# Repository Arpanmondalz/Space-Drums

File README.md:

# Space Drums

Space Drums is an open source computer vision-based air drumming system. It utilizes a smartphone as a wireless camera to track hand positions via MediaPipe and ESP32-based drumsticks to trigger hits via UDP.

This project enables a virtual drum kit experience in mid-air with real-time audio feedback.

---

## Project Structure

The repository is organized into three primary components:

*   **linux-server/**: The optimized Python server for Linux systems. Recommended for lowest latency.
*   **windows-server/**: The standard Python server for Windows 10 and 11.
*   **firmware/**: C++ firmware for the ESP32-based drumsticks.

---

## Hardware Requirements

*   **Computer**: A laptop or desktop running Linux (Ubuntu/Mint) or Windows 10/11.
*   **Smartphone**: Any modern smartphone with a camera and web browser (used as the video source).
*   **Space Drum sticks**
*   **Network**: Both the computer and smartphone must be connected to the same WiFi network.

---

## Version Comparison

### Linux Version (Recommended)
Optimized for high performance. It utilizes direct kernel access for video (V4L2) and audio (ALSA), achieving sub-10ms audio response and superior frame rate stability. It supports high-priority process scheduling.

### Windows Version
Easier to set up using standard Windows drivers (DirectShow). While latency is slightly higher due to the Windows audio stack, it is fully functional for standard use.

---

## Installation and Setup

### 1. ESP32 Firmware
Flash the code located in the `firmware/` folder to your ESP32 boards.

1.  Open the project in the Arduino IDE or PlatformIO.
2.  Update the WiFi credentials (`SSID` and `PASSWORD`) in the source code.
3.  Flash one stick configured as **LEFT** and the other as **RIGHT** (refer to the definitions at the top of the firmware file).

### 2. Python Server Setup
Ensure Python 3.10 or newer is installed.

#### Linux Setup
Navigate to the `linux-server/` directory and run:
```bash
sudo apt-get install libgl1 libasound2-dev
python3 -m venv venv
source venv/bin/activate
pip install -r requirements.txt
```
*Note: Granting high-priority permissions to the Python executable is recommended for optimal performance.*

#### Windows Setup
Navigate to the `windows-server/` directory in PowerShell:
```powershell
python -m venv venv
.\venv\Scripts\Activate
pip install -r requirements.txt
```

### 3. Audio Files

All audio files can be downloaded from the sounds/ folder

---

## Running the System

1.  **Start the Server:**
    *   **Linux:** `venv/bin/python main.py`
    *   **Windows:** `python main.py`

2.  **Connect the Camera:**
    *   The terminal will display a local IP address (e.g., `http://192.168.1.15:5000`).
    *   Open this address in your smartphone's web browser.
    *   Select **Connect** and grant camera permissions.
    *   Position the phone camera to capture your movements.

3.  **Power on the Sticks:**
    *   Turn on the ESP32 drumsticks.
    *   Only the first time: You will need to connect to the "AirDrums-Stick" wifi network and add your wifi SSID and password for each stick
    *   They will automatically discover the server over UDP.
    *   A confirmation sound will play once both sticks are synchronized.

---

## Troubleshooting

*   **Firewall:** Ensure the computer allows incoming connections on **TCP port 5000** (Video) and **UDP port 5556** (Drum Hits).
*   **Audio Latency:**
    *   **Linux:** Ensure you are using the ALSA configuration provided in the code.
    *   **Windows:** If jitter occurs, set the Python process priority to "Realtime" in the Task Manager.

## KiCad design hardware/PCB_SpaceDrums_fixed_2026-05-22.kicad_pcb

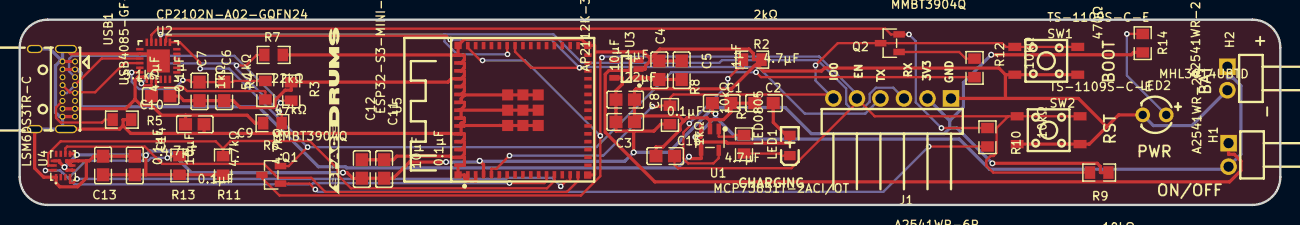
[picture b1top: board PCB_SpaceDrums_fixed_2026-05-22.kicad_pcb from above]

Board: 2 copper layers, 136.1 x 20.0 mm, 44 parts (0 on the bottom side), 28 nets.

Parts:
C1, C2, C7, C10: 4.7µF; C0805
C3: 22µF; C0805
C4, C12, C14: 10µF; C0805
C5, C8: 1µF; C0805
C6, C9, C11, C13, C15: 0.1µF; C0805
H1, H2: A2541WR-2P; HDR-TH_2P-P2.54-H-M-W10.0
J1: A2541WR-6P; HDR-TH_6P-P2.54-H-M-W10.3
LED1: LED0805; LED0805-RD
LED2: MHL3014UBTD; LED-TH_BD3.9-P2.54-RD
Q1, Q2: MMBT3904Q; SOT-23-3_L2.9-W1.3-P1.90-LS2.4-BR
R1, R4: 1kΩ; R0805
R2: 2kΩ; R0805
R3, R5: 5.1kΩ; R0805
R6: 22kΩ; R0805
R7: 47kΩ; R0805
R8, R9, R10, R12: 10kΩ; R0805
R11, R13: 4.7kΩ; R0805
R14: 470Ω; R0805
SW1, SW2: TS-1109S-C-E; SW-SMD_4P-L4.5-W4.5-P3.00-LS7.0
U1: MCP73831T-2ACI/OT; SOT-23-5_L3.0-W1.7-P0.95-LS2.8-BL
U2: CP2102N-A02-GQFN24; QFN-24_L4.0-W4.0-P0.50-TL-EP2.5
U3: AP2112K-3.3TRG1; SOT-25-5_L2.9-W1.6-P0.95-LS2.8-BL
U4: LSM6DS3TR-C; LGA-14_L3.0-W2.5-P0.50-TL
U5: ESP32-S3-MINI-1-N8; BULETM-SMD_ESP32-S3-MINI-1-N8
USB1: USB4085-GF-A; USC-C-SMD_USB4085-GF-A

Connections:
3V3: C3.1, C8.1, C11.2, C12.2, C13.2, C14.2, J1.2, R8.2, R9.1, R11.2, R13.2, R14.1, U3.5, U4.5, U4.8, U4.12, U5.3
BAT+: C1.2, H1.2, H2.1, U1.3
CP_8: R6.2, R7.2, U2.8
CP_RX: J1.4, U2.20, U5.39
CP_TX: J1.3, U2.21, U5.40
D+: U2.3, USB1.A6, USB1.B6
D-: U2.4, USB1.A7, USB1.B7
DTR: Q2.2, R10.1, U2.23
EN: C15.2, J1.5, Q1.3, R9.2, SW2.1, SW2.2, U5.45
GND: C1.1, C2.1, C3.2, C4.2, C5.1, C6.1, C7.1, C8.2, C9.1, C10.1, C11.1, C12.1, C13.1, C14.1, C15.1, H2.2, J1.1, LED2.1, R2.2, R3.2, R5.2, R7.1, SW1.3, SW1.4, SW2.3, SW2.4, U1.2, U2.2, U2.25, U3.2, U4.1, U4.6, U4.7, U5.1, U5.2, U5.46, U5.47, U5.48, U5.49, U5.50, U5.51, U5.52, U5.53, U5.54, U5.55, U5.56, U5.57, U5.58, U5.59, U5.60, U5.GND, USB1.A1, USB1.A12, USB1.B1, USB1.B12, USB1.S1
INT1: U4.4, U5.14
INT2: U4.9, U5.15
IO0: J1.6, Q2.3, R8.1, SW1.1, SW1.2, U5.4
LED2_2: LED2.2, R14.2
Q1_1: Q1.1, R10.2
Q2_1: Q2.1, R12.1
R1_1: LED1.1, R1.1
RTS: Q1.2, R12.2, U2.19
SCL: R11.1, U4.13, U5.12
SDA: R13.1, U4.14, U5.11
U1_1: R1.2, U1.1
U1_5: R2.1, U1.5
U2_5: C6.2, C7.2, R4.2, U2.5, U2.6
U2_9: R4.1, U2.9
USB1_A5: R3.1, USB1.A5
USB1_B5: R5.1, USB1.B5
VBUS: C2.2, C9.2, C10.2, LED1.2, R6.1, U1.4, U2.7, USB1.A4, USB1.A9, USB1.B4, USB1.B9
V_SYS: C4.1, C5.2, H1.1, U3.1, U3.3

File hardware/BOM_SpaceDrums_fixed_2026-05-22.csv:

"Reference","Qty","Value","DNP","Exclude from BOM","Exclude from Board","Footprint","Datasheet"
"A?","1","A","","","","",""
"C1,C2,C7,C10","4","4.7µF","","","","",""
"C3","1","22µF","","","","",""
"C4,C12,C14","3","10µF","","","","",""
"C5,C8","2","1µF","","","","",""
"C6,C9,C11,C13,C15","5","0.1µF","","","","",""
"H1,H2","2","A2541WR-2P","","","","",""
"J1","1","A2541WR-6P","","","","",""
"LED1","1","LED0805","","","","",""
"LED2","1","MHL3014UBTD","","","","",""
"Q1,Q2","2","MMBT3904Q","","","","",""
"R1,R4","2","1kΩ","","","","",""
"R2","1","2kΩ","","","","",""
"R3,R5","2","5.1kΩ","","","","",""
"R6","1","22kΩ","","","","",""
"R7","1","47kΩ","","","","",""
"R8,R9,R10,R12","4","10kΩ","","","","",""
"R11,R13","2","4.7kΩ","","","","",""
"R14","1","470Ω","","","","",""
"SW1,SW2","2","TS-1109S-C-E","","","","",""
"U1","1","MCP73831T-2ACI/OT","","","","",""
"U2","1","CP2102N-A02-GQFN24","","","","",""
"U3","1","AP2112K-3.3TRG1","","","","",""
"U4","1","LSM6DS3TR-C","","","","",""
"U5","1","ESP32-S3-MINI-1-N8","","","","",""
"USB1","1","USB4085-GF-A","","","","",""

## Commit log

2026-02-11 Add Windows setup guide for Air Drums server
    This guide provides detailed steps for setting up the Air Drums server on Windows, including prerequisites, project setup, library installation, network configuration, and troubleshooting common issu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
2026-02-11 added python server
2026-02-11 Add ESP32-S3 Firmware Upload Guide
    This guide outlines the steps to configure the Arduino IDE and upload firmware to the ESP32-S3 Dev Module, including prerequisites, IDE configuration, hardware connection, bootloader mode entry, code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
2026-02-11 Added firmware
2026-02-11 Add note for STICK_ID configuration
    Added a note about updating STICK_ID based on the stick used.
2026-02-11 Revise README with detailed project overview
    Expanded project description and installation instructions.
2026-02-11 Add readme for audio files in Space Drums
2026-02-11 Added sounds
2026-02-11 Add Linux setup guide for Air Drums server
    This guide provides detailed instructions for setting up the Air Drums server on Linux, including prerequisites, system dependencies, virtual environment setup, high-performance configuration, firewa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
2026-02-11 added python server for linux
2026-02-11 Add connection instructions for ESP32 drumsticks
    Added instructions for connecting to the 'AirDrums-Stick' wifi network and configuring wifi SSID and password.
2026-02-11 Add wifi connection note to install guide
    Added note about connecting to the 'AirDrums-Stick' wifi network and configuring SSID and password.
2026-02-13 Increase timeout for offline stick reset from 10 to 20 seconds
2026-02-16 Added icon and removed connection message
    Added routes for serving icon and manifest files, updated manifest to include landscape orientation and icon details.
2026-02-16 Upload icon png
2026-02-16 fixed png icon
2026-02-17 Added kick drum to server
2026-02-17 Implement kick sound and update UDP logic
    Added kick sound support and updated UDP handling for kick messages.
2026-02-17 Added better kick sound
2026-02-17 Add kick firmware for ESP32-S3 with IMU support
2026-02-19 Update drum zones and add ride
2026-02-19 reduced cymbal height
2026-02-20 Implement Kalman filter and headless mode for performance
    Add performance enhancements with Kalman filter and headless mode.
2026-02-20 Added kalman smoothing filter and headless mode
2026-02-20 Added 40ms debounce
2026-02-20 Added debounce
2026-02-20 Enhance Linux setup guide with Fedora details
    Updated the Linux setup guide to include Fedora support and clarified installation instructions.
2026-02-23 Added pygame frontend with volume sliders for each drum
2026-02-23 Added pygame ui with volume mixer
2026-03-02 Add initial README for Android version
2026-03-02 Added android studio files
2026-03-02 Add temporary file in gradle wrapper directory
2026-03-02 added gradle files
2026-03-02 Add build directory to .gitignore
2026-03-02 added app files
2026-03-02 Add Android version of Space Drums
2026-03-02 Remove APK from source
2026-03-06 Updated version 1.1
2026-03-06 Move Android project into Android folder
2026-03-06 Updated version with better tracking
2026-03-06 Create readme.md for SpaceDrums Android app
    Added detailed readme for SpaceDrums Android app, covering features, physics engine, tech stack, and setup requirements.
2026-04-06 Added hardware files
2026-05-22 Added Kicad files and BOM
